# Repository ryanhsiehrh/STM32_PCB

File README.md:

# STM32_PCB
PCB centered around the STM32F103C8T6 microcontroller developed in Kicad. This project taught me the main principles of schematic design, pinout planning with STM32CubeMX, power regulation using LDOs, and implementing hardware communication like I2C, UART, SWD, and USB.

**Schematic:**

**PCB:**

## Hardware Components

* **Microcontroller:** STM32F103C8T6.
* **Power:** Onboard 5V-to-3.3V LDO regulator with ferrite bead noise filtering.
* **Clock:** 16 MHz external crystal oscillator.
* **USB & Debug:** Micro-B USB  with standard 4-pin SWD programming pins.
* **Input/Output:** UART, I2C (with built-in pull-ups), and a BOOT0 switch.

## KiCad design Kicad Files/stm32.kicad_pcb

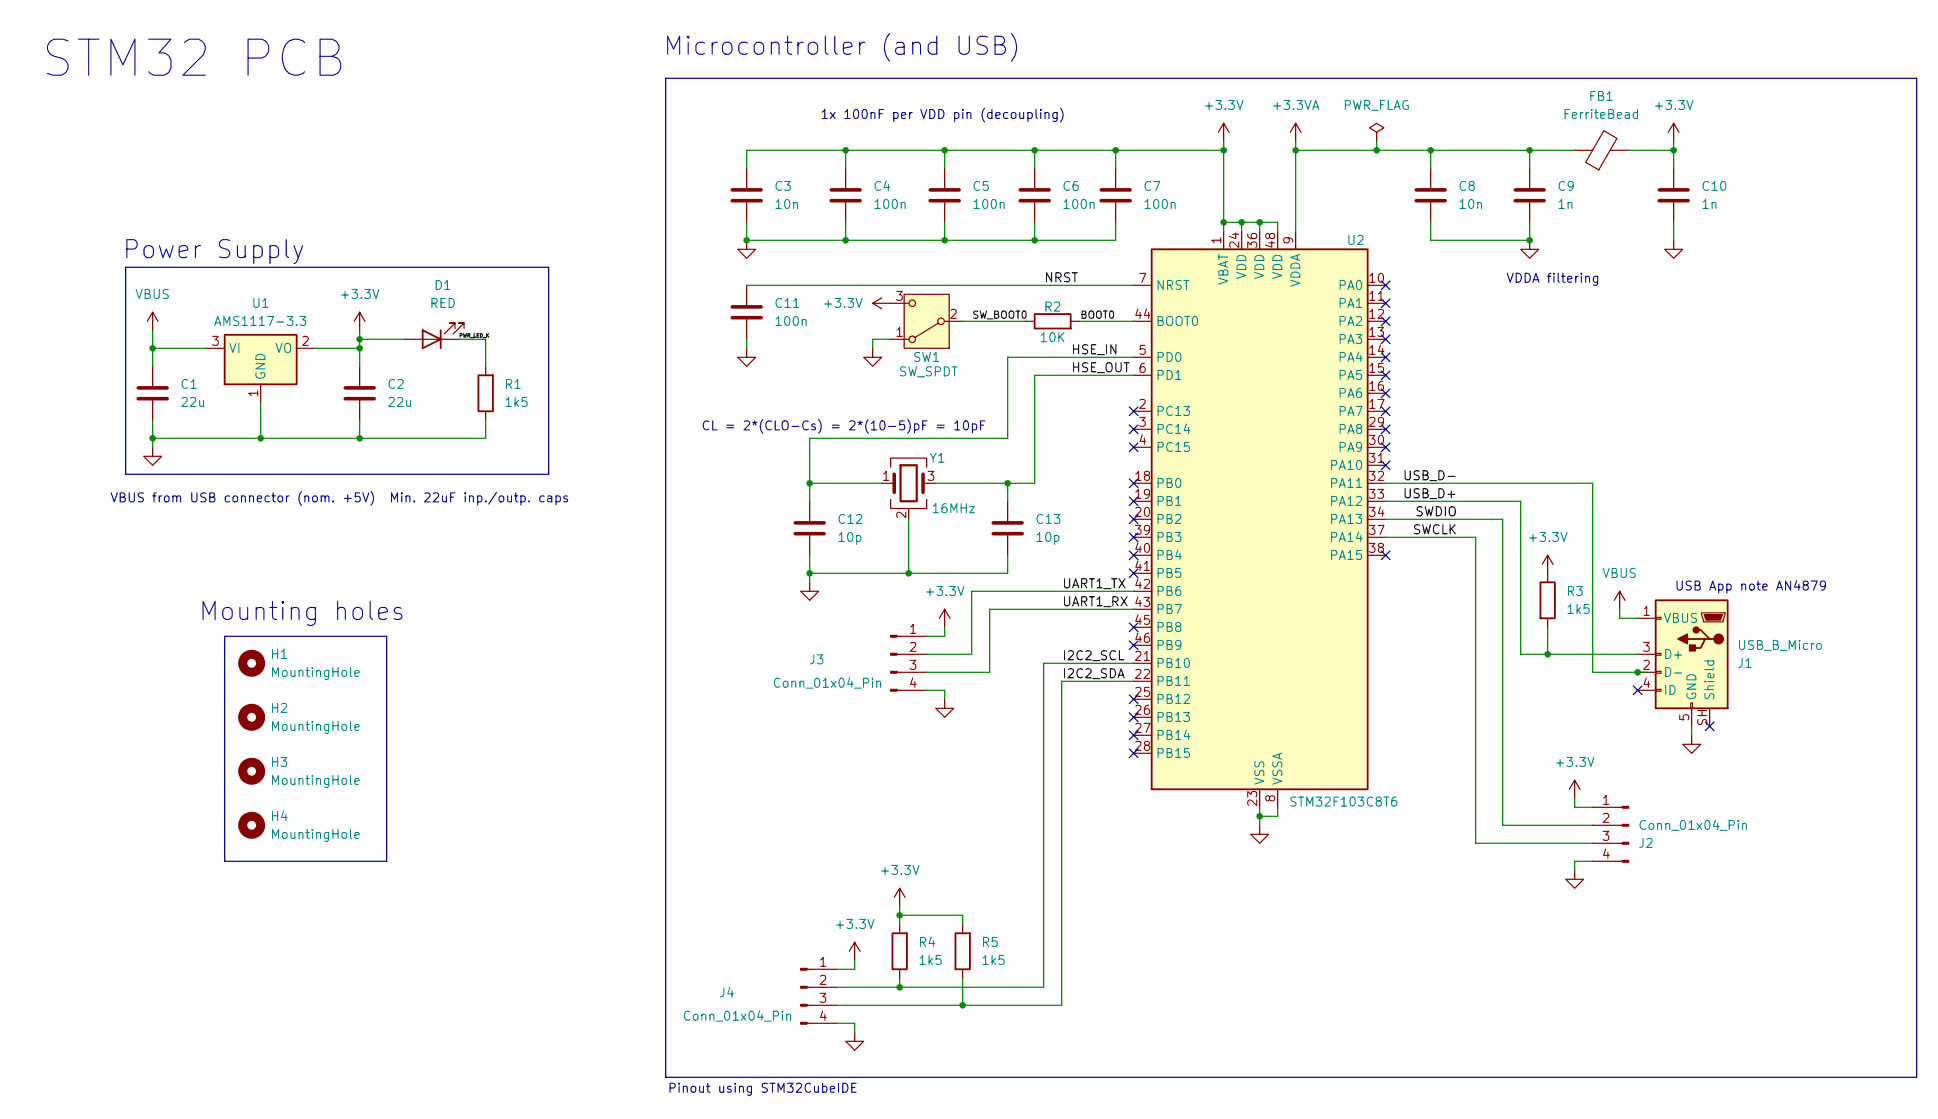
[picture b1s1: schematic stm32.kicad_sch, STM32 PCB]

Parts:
C1, C2: 22u; C_0805_2012Metric
C3: 10n; C_0603_1608Metric
C4, C5, C6, C7, C11: 100n; C_0402_1005Metric
C8: 10n; C_0402_1005Metric
C9, C10: 1n; C_0402_1005Metric
C12, C13: 10p; C_0402_1005Metric
D1: RED; LED_0603_1608Metric
FB1: FerriteBead; L_0603_1608Metric
H1, H2, H3, H4: MountingHole; MountingHole_2.2mm_M2
J1: USB_B_Micro; USB_Micro-B_Wuerth_629105150521
J2, J3, J4: Conn_01x04_Pin; PinHeader_1x04_P2.54mm_Vertical
R1, R3, R4, R5: 1k5; R_0402_1005Metric
R2: 10K; R_0402_1005Metric
SW1: SW_SPDT; SW_SPDT_PCM12
U1: AMS1117-3.3; SOT-223-3_TabPin2
U2: STM32F103C8T6; LQFP-48_7x7mm_P0.5mm
Y1: 16MHz; Crystal_SMD_3225-4Pin_3.2x2.5mm

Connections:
+3.3V: C2.1, C3.1, C4.1, C5.1, C6.1, C7.1, C10.1, D1.2 (A), FB1.2, J2.1, J3.1, J4.1, R3.1, R4.2, R5.2, SW1.3 (C), U1.2 (VO), U2.1 (VBAT), U2.24 (VDD), U2.36 (VDD), U2.48 (VDD)
+3.3VA: C8.1, C9.1, FB1.1, U2.9 (VDDA)
/BOOT0: R2.2, U2.44 (BOOT0)
/HSE_IN: C12.1, U2.5 (PD0), Y1.1
/HSE_OUT: C13.1, U2.6 (PD1), Y1.3
/I2C2_SCL: J4.2, R4.1, U2.21 (PB10)
/I2C2_SDA: J4.3, R5.1, U2.22 (PB11)
/NRST: C11.1, U2.7 (NRST)
/PWR_LED_K: D1.1 (K), R1.2
/SWCLK: J2.3, U2.37 (PA14)
/SWDIO: J2.2, U2.34 (PA13)
/SW_BOOT0: R2.1, SW1.2 (B)
/UART1_RX: J3.3, U2.43 (PB7)
/UART1_TX: J3.2, U2.42 (PB6)
/USB_D+: J1.3 (D+), R3.2, U2.33 (PA12)
/USB_D-: J1.2 (D-), U2.32 (PA11)
GND: C1.2, C2.2, C3.2, C4.2, C5.2, C6.2, C7.2, C8.2, C9.2, C10.2, C11.2, C12.2, C13.2, J1.5 (GND), J2.4, J3.4, J4.4, R1.1, SW1.1 (A), U1.1 (GND), U2.8 (VSSA), U2.23 (VSS), U2.35 (VSS), U2.47 (VSS), Y1.2 (G), Y1.4 (G)
VBUS: C1.1, J1.1 (VBUS), U1.3 (VI)

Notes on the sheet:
Microcontroller (and USB)
CL = 2*(CLO-Cs) = 2*(10-5)pF = 10pF
USB App note AN4879
STM32 PCB
Mounting holes
VDDA filtering
1x 100nF per VDD pin (decoupling)
Pinout using STM32CubeIDE
Power Supply
VBUS from USB connector (nom. +5V) Min. 22uF inp./outp. caps

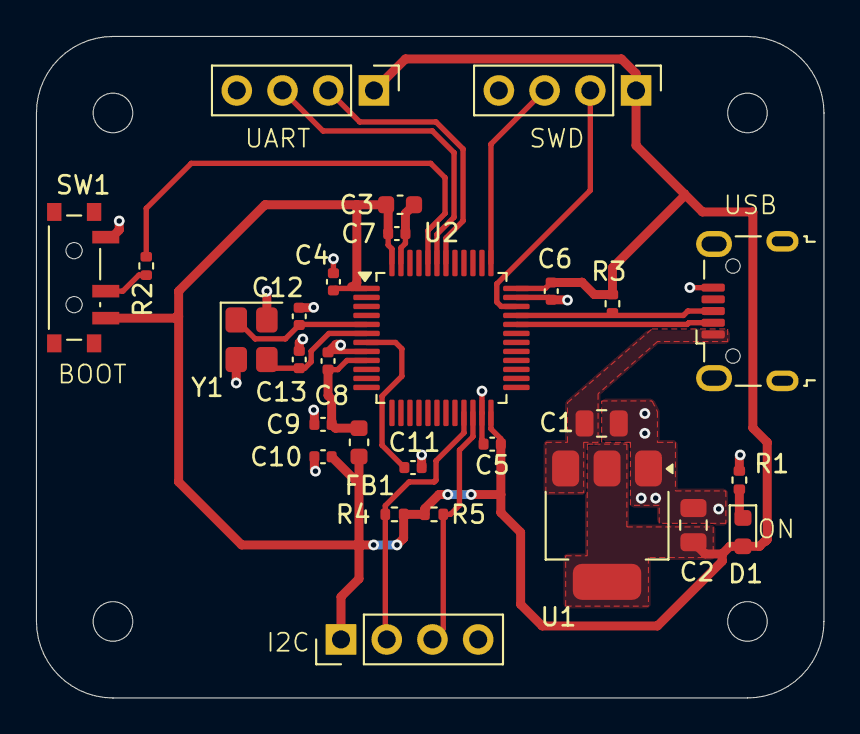
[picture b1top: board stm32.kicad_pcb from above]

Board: 2 copper layers, 43.8 x 36.8 mm, 32 parts (0 on the bottom side), 18 nets.
